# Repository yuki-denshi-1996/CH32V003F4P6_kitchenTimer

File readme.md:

<!---
 SPDX-FileCopyrightText: 2024 yuki-denshi-1996 <matsukawa.software@gmail.com>
 SPDX-License-Identifier: BSD 3-Clause
--->
# 目次
- [目次](#目次)
- [はじめに](#はじめに)
- [gitのディレクトリ構成](#gitのディレクトリ構成)
- [基板に使用した部品等](#基板に使用した部品等)
- [標準プログラムでの使い方](#標準プログラムでの使い方)
- [プログラムの変更](#プログラムの変更)
- [仕様](#仕様)
- [ライセンス](#ライセンス)
- [連絡先](#連絡先)

# はじめに
これはCH32V003F4P6でタイマーを作ろうというプロジェクトです。<BR>

# gitのディレクトリ構成
CH32V003F4P6_Timer_2024_Kit ディレクトリにプログラムが入っています。MounRiver Studioにて開発しています。プロジェクトごと読み込んでください。<BR>
timer_V1 ディレクトリに基板データが入っています。KiCad 8.0で設計しています。timer_V1.kicad_pro を読み込んでください。<BR>

# 基板に使用した部品等
ここに出しているものは、あくまでも推奨しているものです。自由に変更していただいて構いません。<BR>
ここに書いているものは、すべて秋月電子通商様で購入できる部品となっています。<BR>
|   部品番号  |  部品名   |  リンク   | 備考|
| --- | --- | --- | ---|
| BZ1  |  圧電スピーカー   |  https://akizukidenshi.com/catalog/g/g104118/   | |
|    C1 |   セラミックコンデンサ 0.1uF  | https://akizukidenshi.com/catalog/g/g113582/  |  |
|     D1|   SBD  |   https://akizukidenshi.com/catalog/g/g116384/  |  |
| F1  |   リセッタブルヒューズ  |  https://akizukidenshi.com/catalog/g/g101354/   | |
|  J2  |   電源コネクタ (XH-2コネクタ)  |  https://akizukidenshi.com/catalog/g/g112247/   |  |
|  Q1-Q4   |   DTA123E (デジタルトランジスタ)  |  https://akizukidenshi.com/catalog/g/g112465/   |  |
| R1-R8, R10 |   抵抗 1kΩ (1/6Wサイズ)  |  https://akizukidenshi.com/catalog/g/g116102/   | |
|    SW1-SW6 |   タクトスイッチ  | https://akizukidenshi.com/catalog/g/g101282/    |  |
|     U2|  E40364-IFOW (時計用7セグメントLED)   |   https://akizukidenshi.com/catalog/g/g114426/  |  |
| U3  |   CH32V003F4P6 (マイコン)  |  https://akizukidenshi.com/catalog/g/g118061/   | |

# 標準プログラムでの使い方
ここでは、プログラムを改変していないことを前提条件として、使い方を記します。<BR>

まず電源を入れます。<BR>

MINスイッチで分数を, SECスイッチで秒数を変更することができます。<BR>
スタート・ストップをする場合には、START/STOPスイッチを押してください。<BR>
クリア(0分0秒に戻す)場合には、MINボタンとSECボタンを同時におしてください。<BR>

次にFASTボタンの説明です。<BR>
このタイマーには時刻を記憶できるボタンが2つ付いています。<BR>
登録したい時間をMIN/SECスイッチで設定したあと、FASTスイッチをピッとなるまで長押しします<BR>
次回以降は、登録した方のボタンを押すだけで、時間がセットされます<BR>
FASTボタンは2つありますので、2つの時間を記憶しておけます。<BR>

最後にストップウォッチモードの説明です。<BR>
0分0秒の状態でSTART/STOPを押すと、ストップウォッチになり、時間がカウントされます。<BR>

なお、動作していない状態(時間を測定していない状態)でしばらく放置しておくと、自動的に消灯し、スリープモードに入ります。<BR>
復帰する場合には、MIN/SEC/START・STOPボタンのいずれかを押してください。<BR>

# プログラムの変更
使用するピンは、圧電スピーカーが接続されているピン(PC5)を除き、自由に変更できます。<BR>
変更する場合は、プログラムソースにあるUser/Timer_2024_Kit.hの宣言を変更してください。<BR>

````diff
//PIN定義
-#define SEG_A PC2
+#define SEG_A PD1
#define SEG_B PC4
#define SEG_C PD3
#define SEG_D PC7
#define SEG_E PC6
#define SEG_F PC3
#define SEG_G PD4
#define SEG_DOT PD2
````

注意：PA1, PA2はプッシュプル出力/(プルアップ・プルダウンを使用しない)入力のみ可能です。基本的には変更しないことをおすすめします。

また、タイマーのビープ音は、Timer_2024_Kit.hのBEEP_FREQで変更できます。使用したい周波数を入れてください。
````diff
//BEEP音の高さ
-#define BEEP_FREQ 2000
+#define BEEP_FREQ 2500 //2500Hzに設定
````
その他、細かい設定もTimer_2024_Kit.hにて変更可能です。

# 仕様
電源は乾電池3本 (1.5V x 3 = 4.5V)を使用することを前提としていますが、USB電源等5Vでも使えます。

# ライセンス
このプログラムにはBSD 3-Clauseライセンスが適用されています。<BR>
詳しくは[3条項BSDライセンス](https://licenses.opensource.jp/BSD-3-Clause/BSD-3-Clause.html)をご覧ください。

# 連絡先
バグや追加機能の実装等はGithubのissueに書き込んでください。<BR>
ライセンス・再配布・その他問い合わせについては、下のメールアドレスまたはGoogle Formからどうぞ。<BR>
<BR>
メールアドレス:matsukawa.software＠gmail.com (アットマークを半角にしてください)<BR>
[Google Form お問い合わせフォーム](https://denshi1996.com/?page_id=68#toc1)<BR>

©️2024 - Yuki (denshi-1996) 以上

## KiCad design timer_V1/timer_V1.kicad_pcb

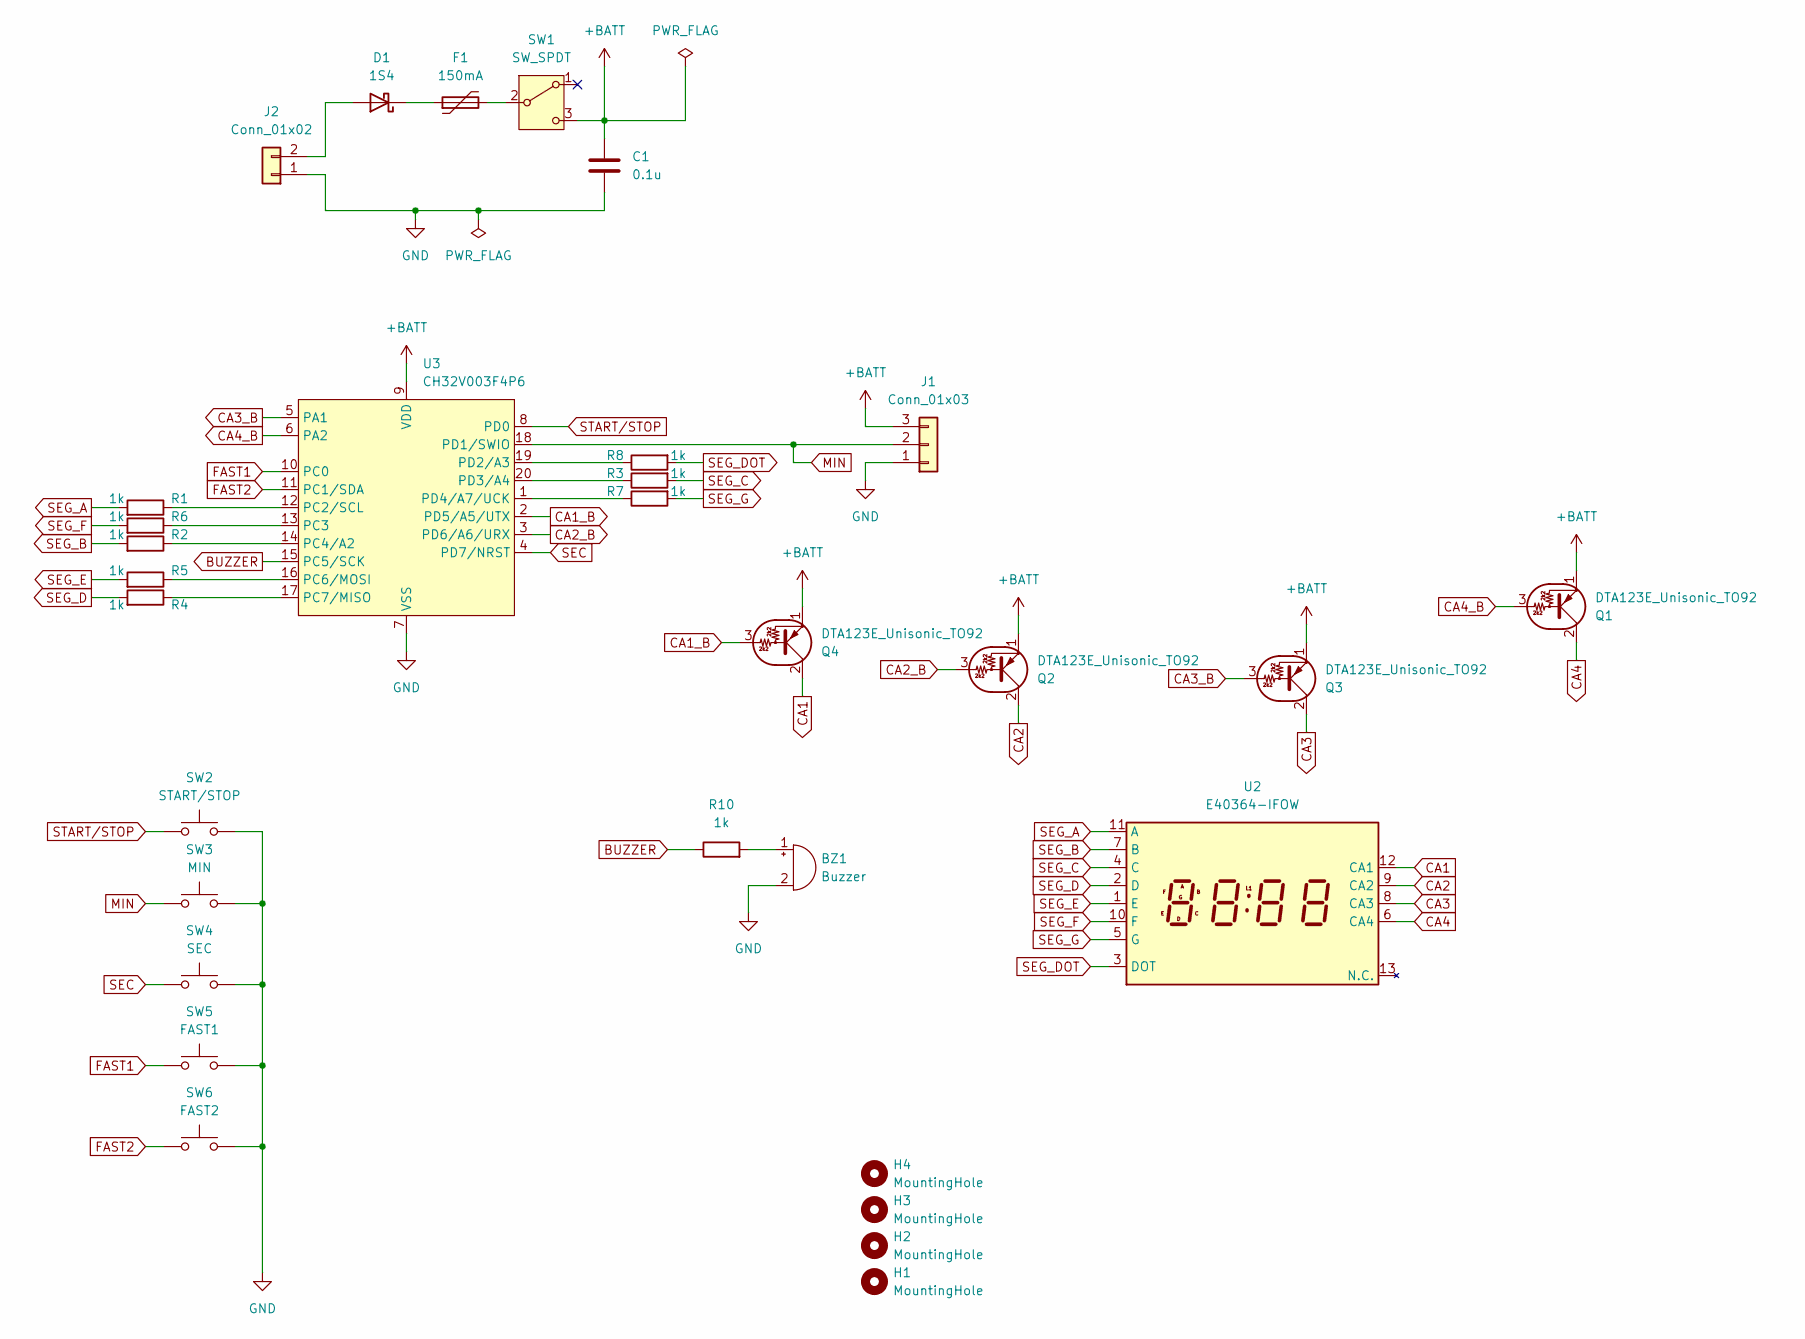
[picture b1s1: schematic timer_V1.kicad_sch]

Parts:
BZ1: Buzzer; AKI_CERAMIC_BUZZER_PKM13EPYH4000-A0
C1: 0.1u; C_DISK_P5.0mm
D1: 1S4; R_1_4W
F1: 150mA; R_1_6W
H1, H2, H3, H4: MountingHole; PAD_3mm_5mm
J1: Conn_01x03; PinHeader_1x03_Program
J2: Conn_01x02; JST_XH_B2B-XH-A_1x02_P2.50mm_Vertical
Q1, Q2, Q3, Q4: DTA123E_Unisonic_TO92; yuki_TO-92_Wide
R1, R2, R3, R4, R5, R6, R7, R8, R10: 1k; R_1_6W
SW1: SW_SPDT; Yuki_Slide_Switch_P2.54
SW2: START/STOP; SW_PUSH_6mm
SW3: MIN; SW_PUSH_6mm
SW4: SEC; SW_PUSH_6mm
SW5: FAST1; SW_PUSH_6mm
SW6: FAST2; SW_PUSH_6mm
U2: E40364-IFOW; E40364-IFOW_DEKAI
U3: CH32V003F4P6; TSSOP-20_4.4x6.5mm_P0.65mm

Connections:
+BATT: C1.1, J1.3, Q1.1 (E), Q2.1 (E), Q3.1 (E), Q4.1 (E), SW1.3 (C), U3.9 (VDD)
BUZZER: R10.1, U3.15 (PC5/SCK)
CA1: Q4.2 (C), U2.12 (CA1)
CA1_B: Q4.3 (B), U3.2 (PD5/A5/UTX)
CA2: Q2.2 (C), U2.9 (CA2)
CA2_B: Q2.3 (B), U3.3 (PD6/A6/URX)
CA3: Q3.2 (C), U2.8 (CA3)
CA3_B: Q3.3 (B), U3.5 (PA1)
CA4: Q1.2 (C), U2.6 (CA4)
CA4_B: Q1.3 (B), U3.6 (PA2)
FAST1: SW5.1, U3.10 (PC0)
FAST2: SW6.1, U3.11 (PC1/SDA)
GND: BZ1.2 (-), C1.2, J1.1, J2.1, SW2.2, SW3.2, SW4.2, SW5.2, SW6.2, U3.7 (VSS)
MIN: J1.2, SW3.1, U3.18 (PD1/SWIO)
unnamed: BZ1.1 (+), R10.2
unnamed: D1.2 (A), J2.2
unnamed: D1.1 (K), F1.1
unnamed: F1.2, SW1.2 (B)
unnamed: R1.1, U3.12 (PC2/SCL)
unnamed: R6.1, U3.13 (PC3)
unnamed: R2.1, U3.14 (PC4/A2)
unnamed: R5.1, U3.16 (PC6/MOSI)
unnamed: R4.1, U3.17 (PC7/MISO)
unnamed: R8.1, U3.19 (PD2/A3)
unnamed: R3.1, U3.20 (PD3/A4)
unnamed: R7.1, U3.1 (PD4/A7/UCK)
SEC: SW4.1, U3.4 (PD7/NRST)
SEG_A: R1.2, U2.11 (A)
SEG_B: R2.2, U2.7 (B)
SEG_C: R3.2, U2.4 (C)
SEG_D: R4.2, U2.2 (D)
SEG_DOT: R8.2, U2.3 (DOT)
SEG_E: R5.2, U2.1 (E)
SEG_F: R6.2, U2.10 (F)
SEG_G: R7.2, U2.5 (G)
START/STOP: SW2.1, U3.8 (PD0)

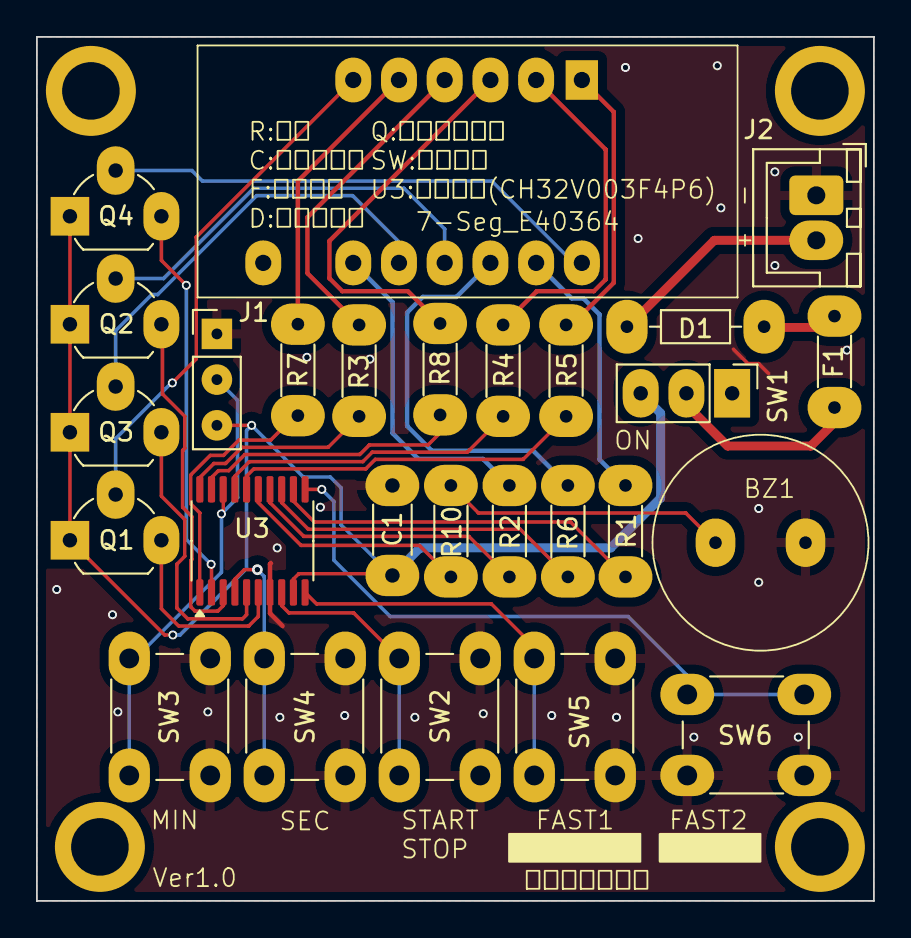
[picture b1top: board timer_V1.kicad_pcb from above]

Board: 2 copper layers, 46.5 x 48.0 mm, 31 parts (0 on the bottom side), 36 nets.

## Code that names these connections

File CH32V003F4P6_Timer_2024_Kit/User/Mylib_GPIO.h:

/*
* SPDX-FileCopyrightText: 2024 yuki-denshi-1996 <matsukawa.software@gmail.com>
* SPDX-License-Identifier: BSD 3-Clause
*/

/*
 * CH32V003F4P6用（CH32V003)GPIO操作ライブラリ
 * Mylib_GPIO.h
 *
 *  Created on: Sep 22, 2024
 *      Author: yuki (denshi-1996)
 */
#include <stdint.h>

#ifndef USER_MYLIB_GPIO_H_
#define USER_MYLIB_GPIO_H_

#define HIGH 1
#define LOW 0

//GPIO定義
#define PA1 0xA1
#define PA2 0xA2

#define PC0 0xC0
#define PC1 0xC1
#define PC2 0xC2
#define PC3 0xC3
#define PC4 0xC4
#define PC5 0xC5
#define PC6 0xC6
#define PC7 0xC7

#define PD0 0xD0
#define PD1 0xD1
#define PD2 0xD2
#define PD3 0xD3
#define PD4 0xD4
#define PD5 0xD5
#define PD6 0xD6
#define PD7 0xD7

//GPIO_MODE
#define INPUT 0b1000
#define F_INPUT 0b1001
#define INPUT_PULLUP 0b1110
#define INPUT_PULLDOWN 0b1010
#define OUTPUT 0b0000
#define OD_OUTPUT 0b0001
#define F_OUTPUT 0b0010
#define F_OD_OUTPUT 0b0011

//GPIO_OUTPUT_SPEED_MODE
#define OUTPUT_SPEED_MODE_10MHz 0b01
#define OUTPUT_SPEED_MODE_2MHz 0b10
#define OUTPUT_SPEED_MODE_50MHz 0b11

//EventGPIO
#define EVENT_RISE 0x01 //Rise(立ち上がり)でイベント発生
#define EVENT_FALL 0x02 //Fall(たち下がり)でイベント発生

//GPIO 初期化（クロック供給）
//GPIOを使う場合は、最初に有効化すること
void GPIOA_init(void);
void GPIOC_init(void);
void GPIOD_init(void);

//AFIO初期化
void AFIO_init(void);

//PINイベント設定関数
//pin:ピン | mode:立ち上がり,たち下がり　どちらか
void eventGPIO(int pin, int mode);

//ピン入出力設定
//pin:ピン番| mode:モード
void pinMode(int pin,int mode);

//ピン出力速度指定関数
//pin:ピン番号|speed_mode:出力スピード設定
int OUTPUT_DEFAULT_SpeedMode(int speed_mode);

//デジタル出力設定
//pin:ピン番号|value:1(HIGH) or 0(LOW)
void digitalWrite(int pin,int value);

//デジタル入力設定
//返り値：Pinの状態|Pin:ピン番号
int digitalRead(int pin);

//bitビット置き換え関数
uint32_t bit_replace(uint32_t data, uint32_t byte, uint8_t len, uint8_t shift);

#endif /* USER_MYLIB_GPIO_H_ */

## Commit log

2024-10-22 [Add] Readme.txt
2024-10-22 [fix] FAST2ボタンが使用できない問題を解決
2024-10-22 [Comment] コメントを追加してわかりやすくしました
2024-11-03 [Add] LICENSEを追加
2024-11-04 [Add] Readme.mdを追加
2024-11-04 [Fix] Readme.mdの変更
